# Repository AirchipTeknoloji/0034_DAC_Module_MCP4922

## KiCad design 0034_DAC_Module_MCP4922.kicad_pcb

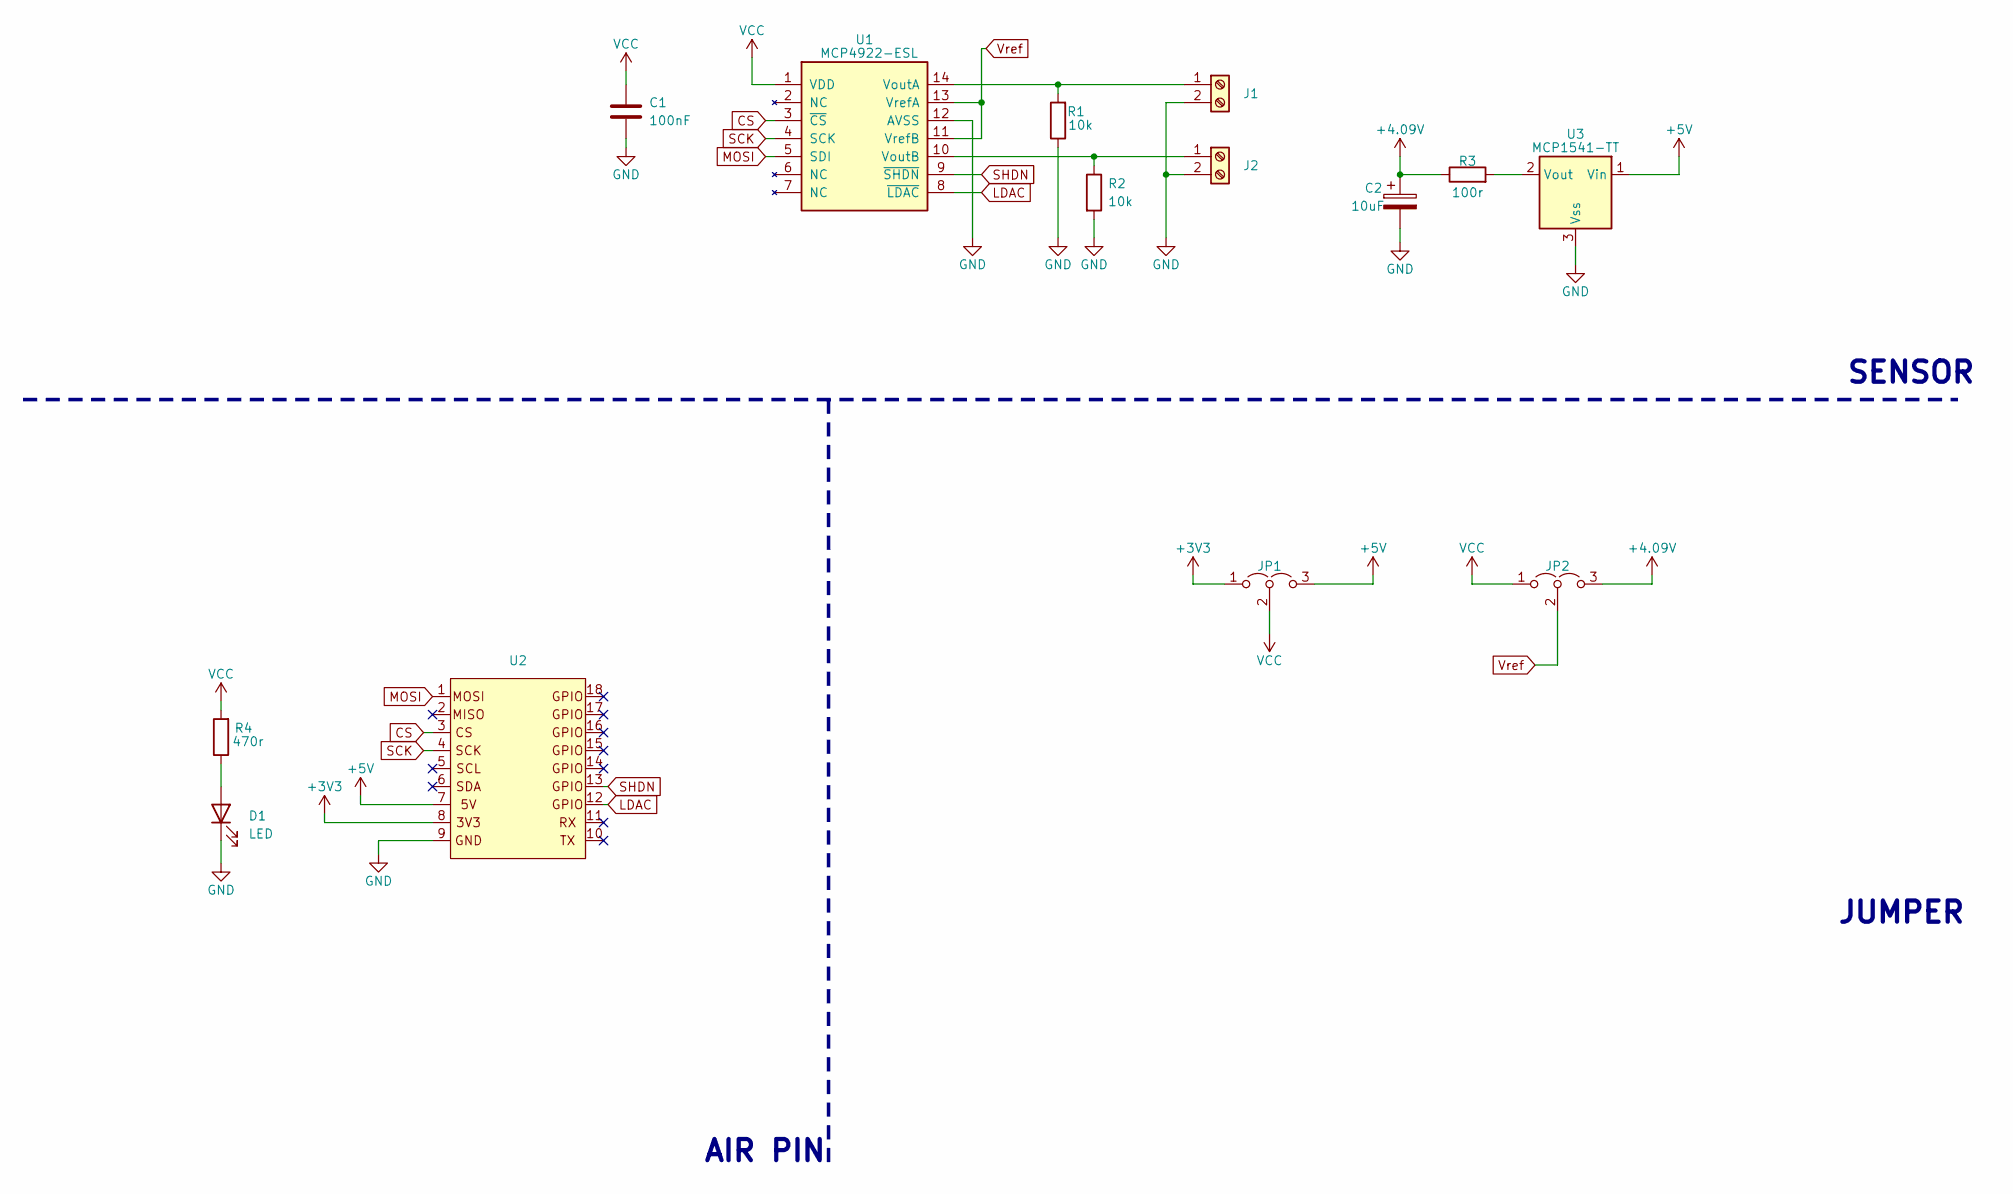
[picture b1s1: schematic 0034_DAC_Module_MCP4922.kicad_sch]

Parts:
C1: 100nF; C_0805_2012Metric
C2: 10uF; CP_EIA-3216-10_Kemet-I
D1: LED; LED_0805_2012Metric
J1, J2: Screw_Terminal_01x02; PinHeader_1x02_P2.54mm_Vertical
JP1, JP2: Jumper_3_Open; SolderJumper-3_P1.3mm_Open_Pad1.0x1.5mm
R1, R2: 10k; R_0805_2012Metric
R3: 100r; R_0805_2012Metric
R4: 470r; R_0805_2012Metric
U1: MCP4922-ESL; SOIC-14_3.9x8.7mm_P1.27mm
U2: pin_header
U3: MCP1541-TT; SOT-23

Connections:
+3V3: JP1.1 (A), U2.8
+4V: C2.1, JP2.3 (B), R3.1
+5V: JP1.3 (B), U2.7, U3.1 (Vin)
CS: U1.3 (~CS), U2.3
GND: C1.2, C2.2, D1.1 (K), J1.2, J2.2, R1.1, R2.2, U1.12 (AVSS), U2.9, U3.3 (Vss)
LDAC: U1.8 (~LDAC), U2.12
MOSI: U1.5 (SDI), U2.1
unnamed: D1.2 (A), R4.1
unnamed: J1.1, R1.2, U1.14 (VoutA)
unnamed: J2.1, R2.1, U1.10 (VoutB)
unnamed: R3.2, U3.2 (Vout)
SCK: U1.4 (SCK), U2.4
SHDN: U1.9 (~SHDN), U2.13
VCC: C1.1, JP1.2 (C), JP2.1 (A), R4.2, U1.1 (VDD)
Vref: JP2.2 (C), U1.11 (VrefB), U1.13 (VrefA)

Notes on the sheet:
SENSOR
JUMPER
AIR PIN

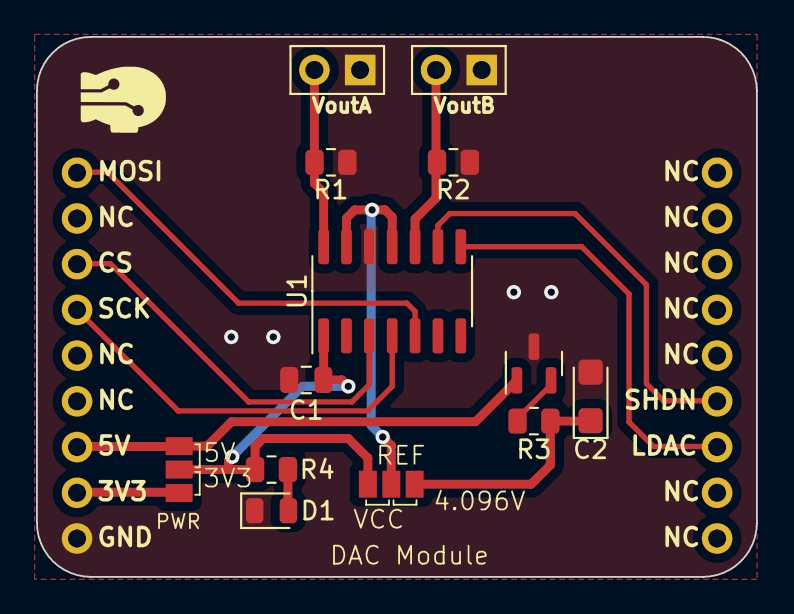
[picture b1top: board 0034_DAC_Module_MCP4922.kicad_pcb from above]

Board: 2 copper layers, 40.0 x 30.0 mm, 14 parts (0 on the bottom side), 15 nets.
